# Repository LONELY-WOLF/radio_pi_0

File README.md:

# radio_pi_0
Device for playing Internet radio stations.

## Hardware
#### Orange Pi Zero
[Orange Pi Zero](http://www.orangepi.org/orangepizero/) or [Orange Pi Zero Plus](http://www.orangepi.org/OrangePiZeroPlus/) board.  H2+ and 256MB RAM should be enough but it's up to you which board to choose.

R1 and Plus2 have no USB A connector. You need to modify interconnection PCB to use these boards.

#### SPI OLED
[diymore.cc 2.42" 128x64 SPI OLED](https://www.diymore.cc/products/2-42-inch-12864-oled-display-module-iic-i2c-spi-serial-for-arduino-c51-stm32-green-white-blue-yellow).
Widely available on Aliexpress.

There is also similar "blue PCB" OLED. I didn't tested it but PCB is different from my black one. Be careful.

#### Remote control
I use MX3 Air Mouse (no backlight, no voice key). And any other RC won't work! If you want to use another one you have to rewrite the code.

#### Interconnection PCB
It's 2 layer PCB. Making this board at home will be pretty hard, so I use JLCPCB service.

All sockets/headers are 2.54mm. Audio connector is Dragon City ST-033.

## Software
Main app is written in C#. It uses ffplay to play audio and HidSharp to get keys from RC.
App was tested on Armbian (based on Ubuntu 18.04).

#### Controls
* Play/pause - starts or stops playing
* Pg+/Pg- - changes station
* Vol+/Vol-/Mute - you know...
* Power key shuts system down in some strange way. NEVER USE IT! Disconnect power source if you did. In future releases I want to make it Reset key.

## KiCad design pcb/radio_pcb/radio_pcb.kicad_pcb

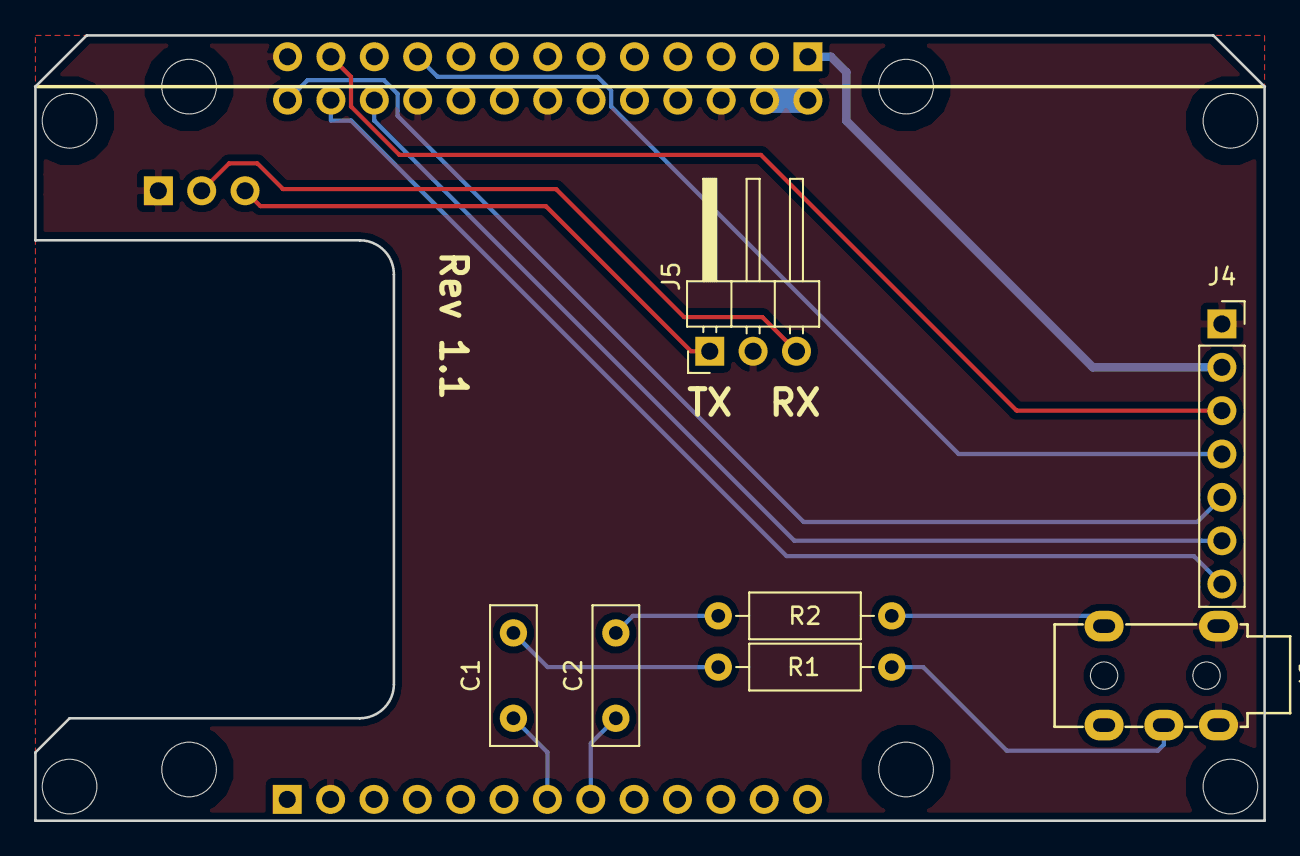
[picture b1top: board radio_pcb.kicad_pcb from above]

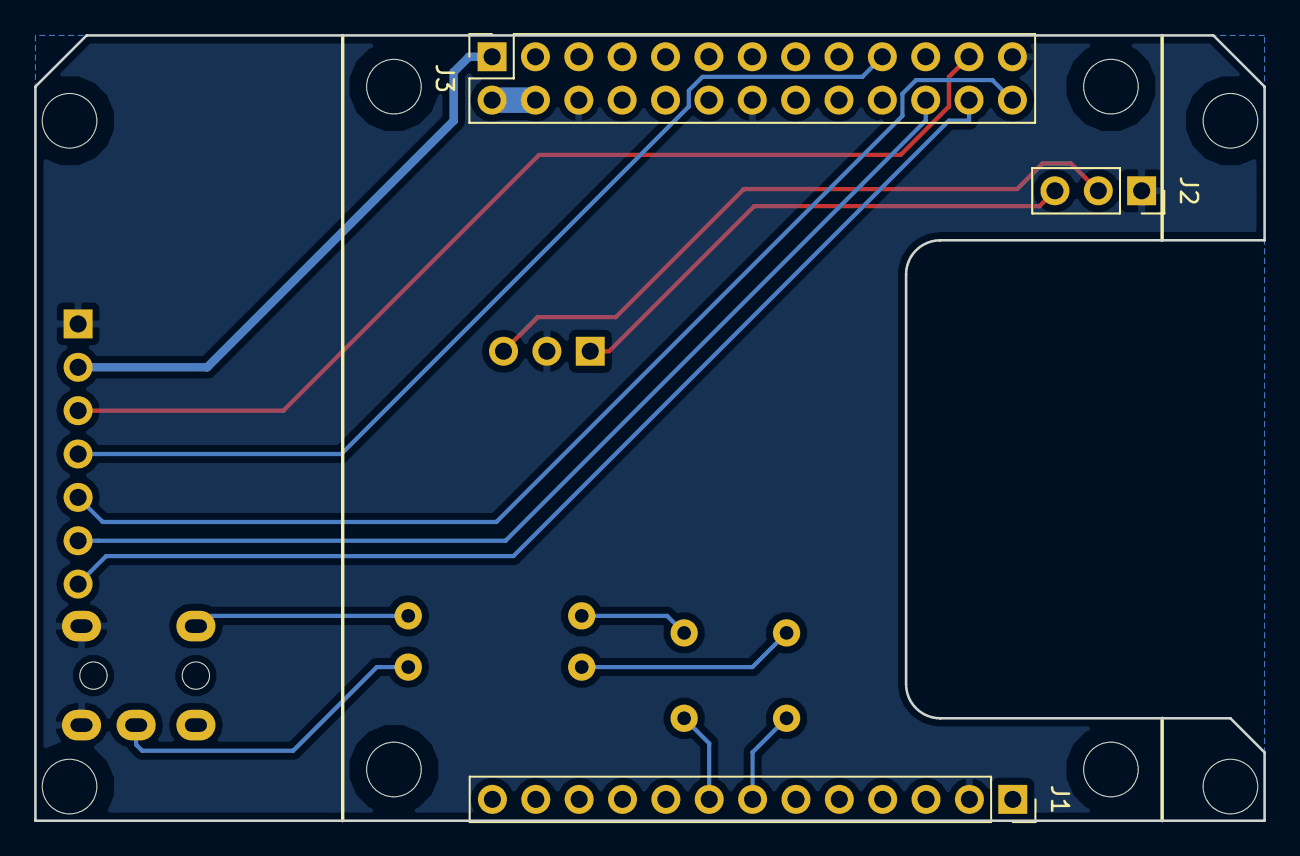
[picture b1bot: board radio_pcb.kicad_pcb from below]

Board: 2 copper layers, 72.0 x 46.0 mm, 10 parts (3 on the bottom side), 16 nets.

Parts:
C1, C2: C_Small; C_Disc_D8.0mm_W2.5mm_P5.00mm
J1: Conn_01x13; PinSocket_1x13_P2.54mm_Vertical
J2: Conn_01x03; PinSocket_1x03_P2.54mm_Vertical
J3: Conn_02x13_Odd_Even; PinSocket_2x13_P2.54mm_Vertical
J4: Conn_01x07; PinSocket_1x07_P2.54mm_Vertical
J5: Conn_01x03; PinHeader_1x03_P2.54mm_Horizontal
J6: AudioJack3_Ground; 3.5mm_5_contacts_3_conductors_audio_plug
R1, R2: R; R_Axial_DIN0207_L6.3mm_D2.5mm_P10.16mm_Horizontal

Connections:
+3V3: J3.1, J4.2
+5V: J3.2, J3.4
/CLK: J3.23, J4.3
/CS: J3.24, J4.7
/DC: J3.22, J4.6
/L: C2.1, J1.8
/MOSI: J3.19, J4.4
/R: C1.1, J1.7
/RES: J3.26, J4.5
/RX: J2.2, J5.3
/TX: J2.3, J5.1
GND: J1.2, J2.1, J3.6, J3.9, J3.14, J3.20, J3.25, J4.1, J5.2, J6.S
unnamed: C1.2, R1.1
unnamed: C2.2, R2.1
unnamed: J6.R, R1.2
unnamed: J6.T, R2.2

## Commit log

2018-12-22 PCB v1.1
2018-12-22 radio_app
2018-12-22 images
2018-12-22 radio_appd.sh
2018-12-23 made src folder
2018-12-23 added some install hints
2019-01-12 refactoring
2019-01-12 new config example
2019-01-13 torch feature
2019-03-20 Brightness down
2019-03-23 ffplay crash fix
2019-05-03 new screensaver
2019-05-04 universal time font support
2019-05-04 new modes implementation
2019-05-05 crash fix
2019-05-05 add gitignore
2019-05-05 fix project file
2019-05-05 mode change lag removed
2019-05-12 Station info page
2019-05-12 new Draw() safety implementation
2020-07-04 Change channels with numpad
